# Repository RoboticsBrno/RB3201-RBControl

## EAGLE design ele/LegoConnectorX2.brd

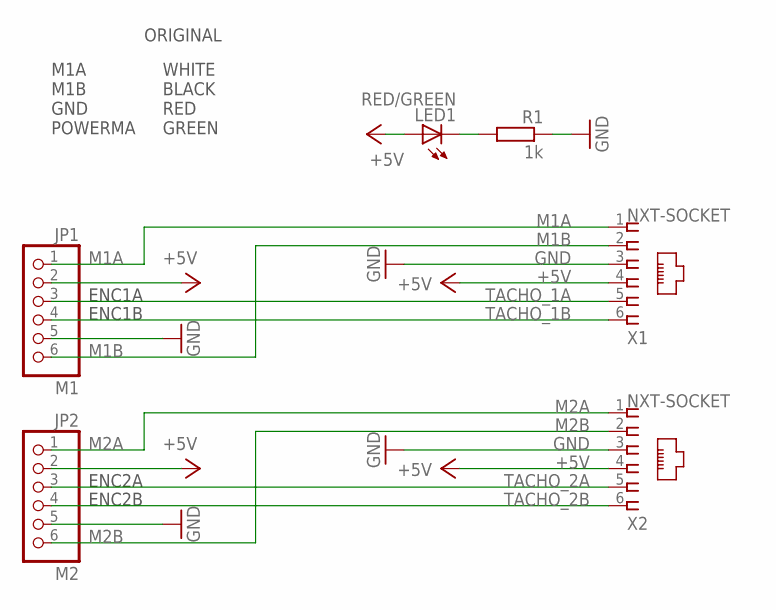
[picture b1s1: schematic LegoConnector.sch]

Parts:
JP1: M1; 1X06
JP2: M2; 1X06
LED1: RED/GREEN; SML0603
R1: 1k; R0603
X1, X2: NXT-SOCKET

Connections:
+5V: JP1.2, JP2.2, LED1.A, X1.4, X2.4
GND: JP1.5, JP2.5, R1.1, X1.3, X2.3
M1A: JP1.1, X1.1
M1B: JP1.6, X1.2
M2A: JP2.1, X2.1
M2B: JP2.6, X2.2
unnamed: LED1.C, R1.2
TACHO_1A: JP1.3, X1.5
TACHO_1B: JP1.4, X1.6
TACHO_2A: JP2.3, X2.5
TACHO_2B: JP2.4, X2.6

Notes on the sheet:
WHITE BLACK RED GREEN
ORIGINAL
M1A M1B GND POWERMA
ENC1B
ENC1A
ENC2B
ENC2A

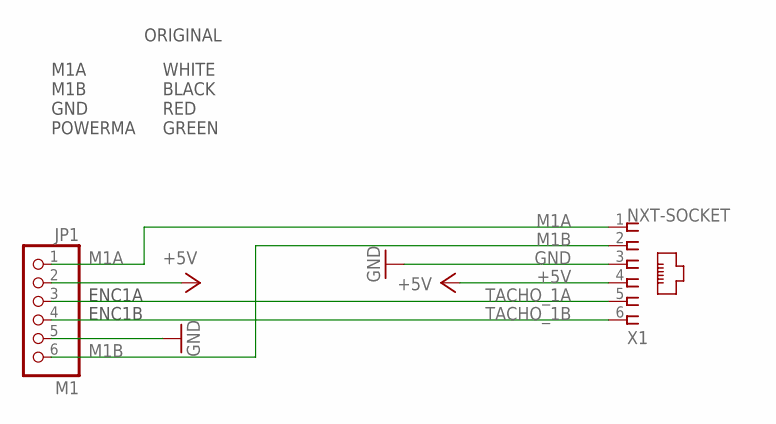
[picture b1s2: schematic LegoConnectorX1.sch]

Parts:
JP1: M1; 1X06
X1: NXT-SOCKET

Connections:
+5V: JP1.2, X1.4; also elsewhere on the board
GND: JP1.5, X1.3; also elsewhere on the board
M1A: JP1.1, X1.1
M1B: JP1.6, X1.2
TACHO_1A: JP1.3, X1.5
TACHO_1B: JP1.4, X1.6

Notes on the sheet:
WHITE BLACK RED GREEN
ORIGINAL
M1A M1B GND POWERMA
ENC1B
ENC1A

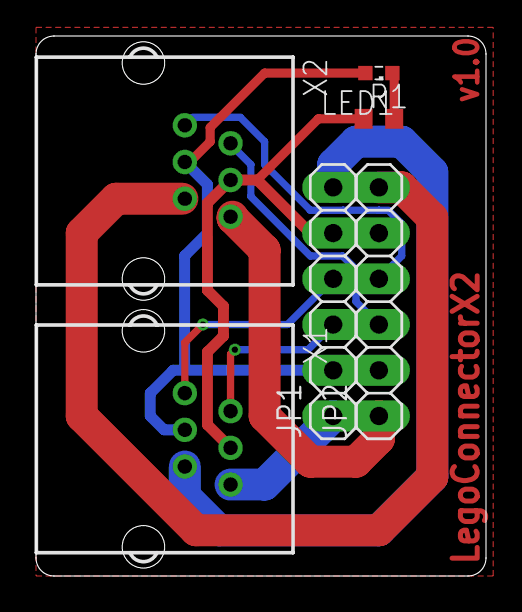
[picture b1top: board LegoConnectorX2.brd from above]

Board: 2 copper layers, 25.0 x 30.0 mm, 6 parts (0 on the bottom side), 11 nets.
